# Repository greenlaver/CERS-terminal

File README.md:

# CERS-terminal

[CERS-terminal](https://github.com/greenlaver/CERS-terminal) is the terminal device developed for [CERS(COVID-19 Entrance Recording System)](https://github.com/Yukiho-YOSHIEDA/CERS).

## Device Design

Schematic and board design files are contained in [KiCad](KiCad).

## Dependencies

Works on ESP32, developed with [Arduino IDE](https://www.arduino.cc/en/main/software).

- [ArduinoHkNfcRw](lib/ArduinoHkNfcRw) : RC-S620S Customized Arduino R/W library
- [U8g2](https://github.com/olikraus/u8g2) : 2.27.6
- [ArduinoJson](https://github.com/bblanchon/ArduinoJson) : 6.14.0

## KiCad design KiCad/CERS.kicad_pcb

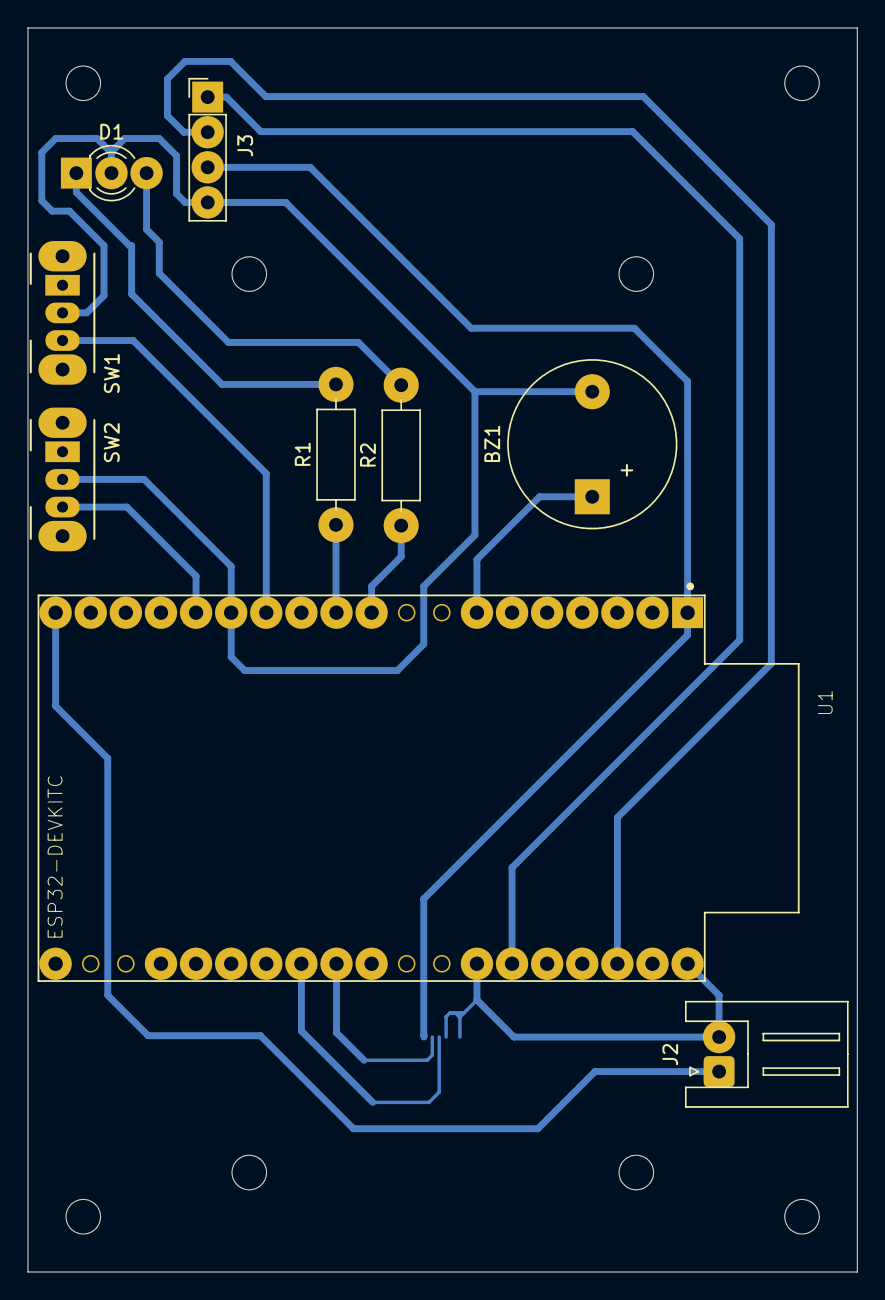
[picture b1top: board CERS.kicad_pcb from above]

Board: 2 copper layers, 60.0 x 90.0 mm, 10 parts (1 on the bottom side), 14 nets.

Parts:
BZ1: Buzzer; Buzzer_12x9.5RM7.6
D1: GL8ED48; LED_D3.0mm-3
J1: NFC; 23287026
J2: PWR; JST_XH_S2B-XH-A_1x02_P2.50mm_Horizontal
J3: OLED; PinHeader_1x04_P2.54mm_Vertical
R1, R2: 1k; R_Axial_DIN0207_L6.3mm_D2.5mm_P10.16mm_Horizontal
SW1: IN/OUT; SW_CuK_OS102011MA1QN1_SPDT_Angled
SW2: CONF; SW_CuK_OS102011MA1QN1_SPDT_Angled
U1: ESP32-DEVKITC; XCVR_ESP32-DEVKITC

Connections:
+3V3: J1.1, J3.3, U1.1
+5V: J2.1, U1.19
GND: BZ1.2, D1.2, J1.4, J1.6, J2.2, J3.4, SW1.2, SW2.2, U1.14, U1.32, U1.38
unnamed: BZ1.1, U1.7
unnamed: D1.1, R1.2
unnamed: D1.3, R2.2
unnamed: J1.2, U1.28
unnamed: J1.3, U1.27
unnamed: J3.1, U1.33
unnamed: J3.2, U1.36
unnamed: R1.1, U1.11
unnamed: R2.1, U1.10
unnamed: SW1.3, U1.13
unnamed: SW2.3, U1.15

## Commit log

2020-03-18 Add documents.
2020-03-18 Add KiCad files.
2020-03-18 Add ESP32 firmware.
2020-03-18 Add LED Blinking System using Ticker.
2020-03-19 Add OLED Drawing
2020-03-19 Fix name-encoding, Add Conf-Mode.
2020-03-20 Fix switch configure mode.
2020-03-20 Support POST Request. This is Ver.1.0.0
2020-03-20 Fix README
2020-03-20 Fix R1 value.
2020-03-30 Move src files into src/CERS-terminal dir.
2021-10-20 SSL 対応しようとした
2021-10-20 MxD向けにraspiローカル鯖へリクエストする修正
2021-10-21 ASCII文字が?になる問題を修正
